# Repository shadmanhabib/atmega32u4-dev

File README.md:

# ATmega32u4-Dev
Development board designed around the ATmega32u4 AVR microcontroller in a small and compact form factor.

## Table of Contents
- [ATmega32u4-Dev](#ATmega32u4-Dev)
  - [Table of Contents](#table-of-contents)
  - [About The Project](#about-the-project)
  - [Getting Started](#getting-started)
    - [Prerequisites](#prerequisites)
    - [Installation](#installation)
  - [Usage](#usage)
  - [Changelog](#changelog)

## About The Project
PCB design, fabrication and documentation of an ATmega32u4 based microcontroller board. 

This project was started to develop a system that could be used for rapid prototyping without the use of external programmers or hardware.
The design was based around the following requirements:

1. On-board programming i.e. not require FTDI or ISP.
2. Remain compatible with Arduno Framework i.e. use Arduino Leonardo pinout.
3. Feature LiPo support.
4. Feature USB-C.

## Getting Started
To get a build this project (or parts thereof), these steps may be followed.

### Prerequisites
1. PlatformIO, Microchip Studios or Arduino IDE for code generation and upload.
2. If you want to make changes to the PCB design or would like to generate new fabrication files, an installation of KiCAD is required.

### Installation
1. Manufacture a PCB.
2. Upload code.

## Usage
Examples will be given in future iterations of this file.

_For more examples, please refer to the [Documentation](https://)_

## Changelog
All notable changes to this project will be documented in this section.

The format is based on [Keep a Changelog](https://keepachangelog.com/en/1.0.0/),
and this project attempts to adhere to [Semantic Versioning](https://semver.org/spec/v2.0.0.html).

### [v1.0.0]
#### Initial design
- ATmega32u4 based design.
- Included LiPo power and charge circuit.
- USB-C for LiPo charging, power and programming.

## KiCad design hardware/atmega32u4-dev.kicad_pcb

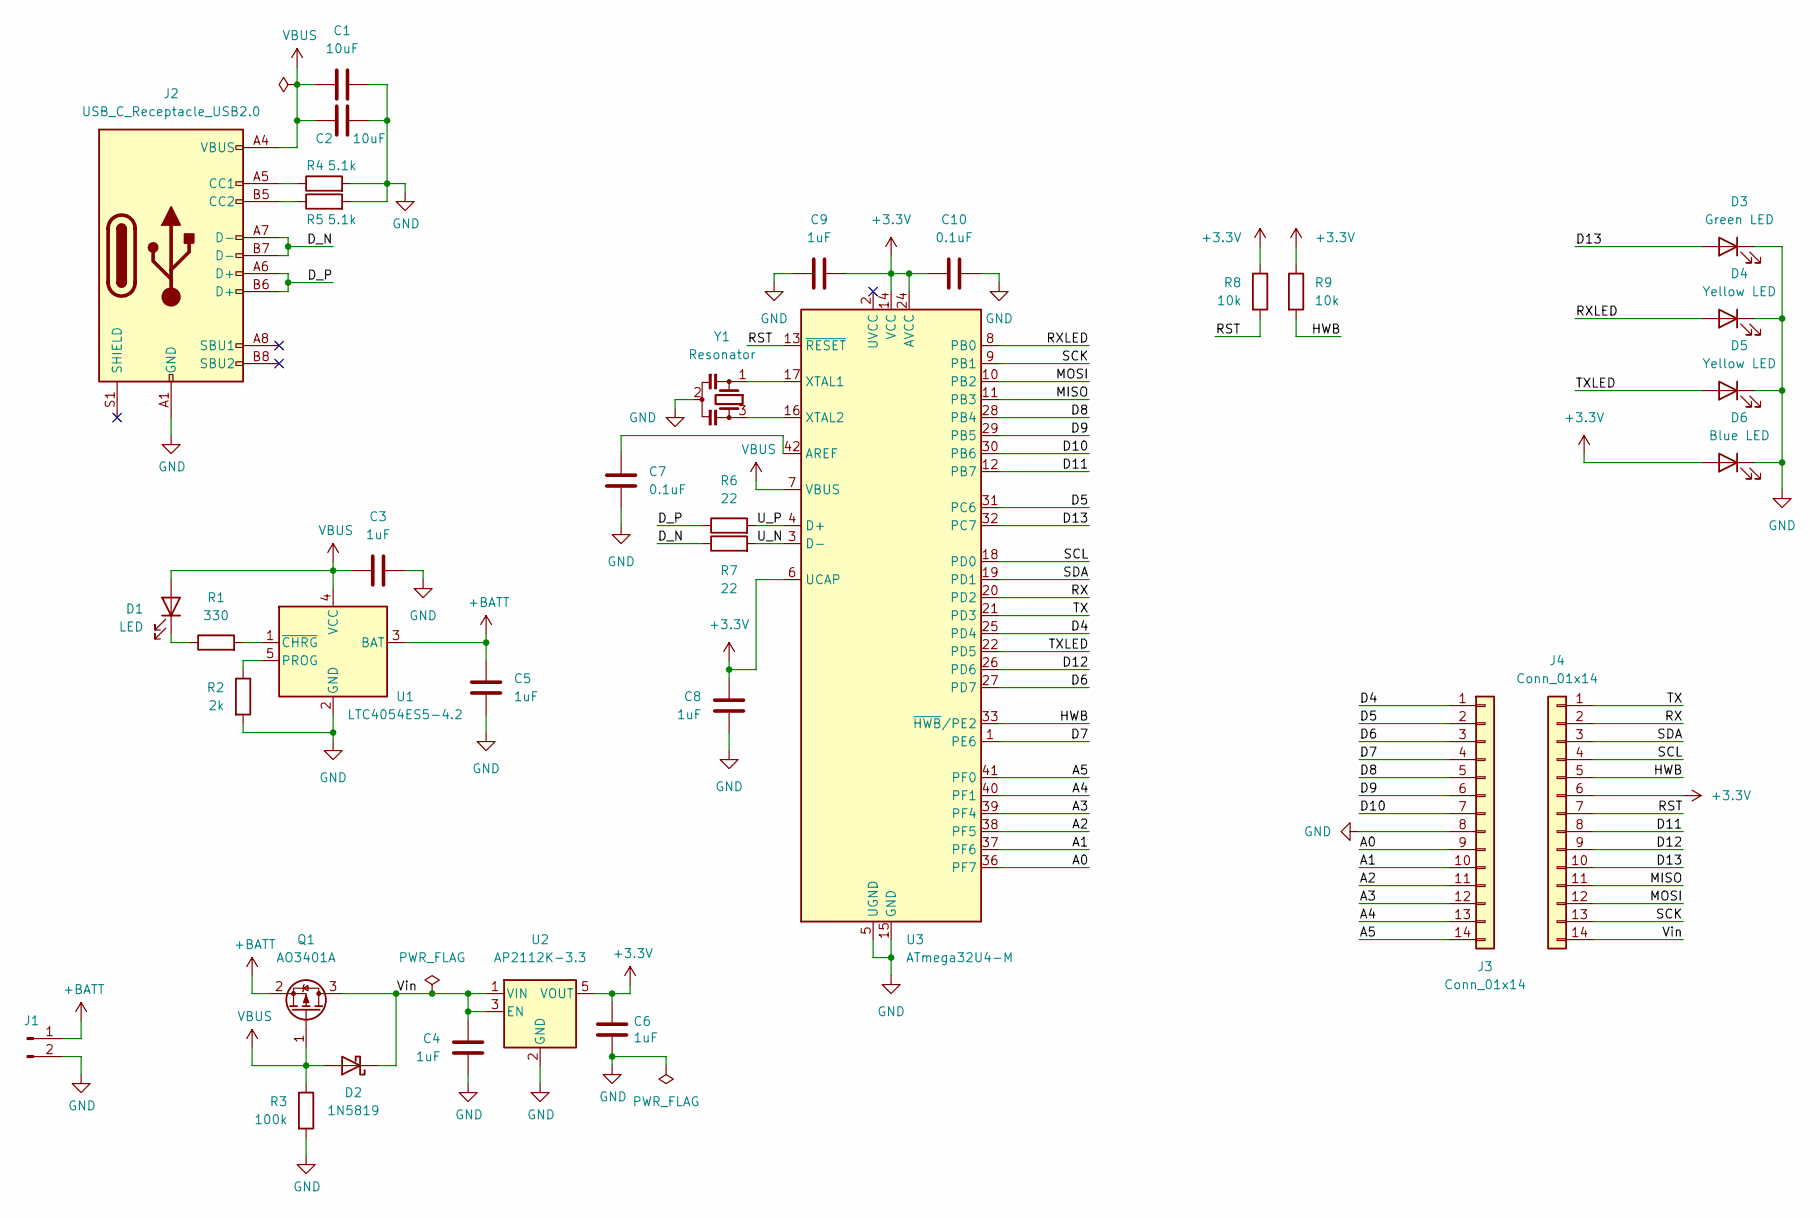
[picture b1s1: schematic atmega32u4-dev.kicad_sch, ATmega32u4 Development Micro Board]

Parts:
C1, C2: 10uF; C_0603_1608Metric
C3, C4, C5, C6, C8, C9: 1uF; C_0603_1608Metric
C7, C10: 0.1uF; C_0603_1608Metric
D1: LED; LED_0603_1608Metric
D2: 1N5819; D_SOD-323
D3: Green LED; LED_0603_1608Metric
D4, D5: Yellow LED; LED_0603_1608Metric
D6: Blue LED; LED_0603_1608Metric
J1: Conn_01x02_Male; JST_PH_S2B-PH-K_1x02_P2.00mm_Horizontal
J2: USB_C_Receptacle_USB2.0; USB_C_Receptacle_Palconn_UTC16-G
J3, J4: Conn_01x14; PinHeader_1x14_P2.54mm_Vertical
Q1: AO3401A; SOT-23
R1: 330; R_0603_1608Metric
R2: 2k; R_0603_1608Metric
R3: 100k; R_0603_1608Metric
R4, R5: 5.1k; R_0603_1608Metric
R6, R7: 22; R_0603_1608Metric
R8, R9: 10k; R_0603_1608Metric
U1: LTC4054ES5-4.2; TSOT-23-5
U2: AP2112K-3.3; SOT-23-5
U3: ATmega32U4-M; QFN-44-1EP_7x7mm_P0.5mm_EP5.2x5.2mm
Y1: Resonator; Resonator_SMD_Murata_CSTxExxV-3Pin_3.0x1.1mm

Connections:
+3V3: C6.1, C8.1, C9.1, C10.1, D6.2 (A), J4.6, R8.1, R9.1, U2.5 (VOUT), U3.6 (UCAP), U3.14 (VCC), U3.24 (AVCC), U3.34 (VCC), U3.44 (AVCC)
+BATT: C5.2, J1.1, Q1.2 (S), U1.3 (BAT)
/A0: J3.9, U3.36 (PF7)
/A1: J3.10, U3.37 (PF6)
/A2: J3.11, U3.38 (PF5)
/A3: J3.12, U3.39 (PF4)
/A4: J3.13, U3.40 (PF1)
/A5: J3.14, U3.41 (PF0)
/D4: J3.1, U3.25 (PD4)
/D5: J3.2, U3.31 (PC6)
/D6: J3.3, U3.27 (PD7)
/D7: J3.4, U3.1 (PE6)
/D8: J3.5, U3.28 (PB4)
/D9: J3.6, U3.29 (PB5)
/D10: J3.7, U3.30 (PB6)
/D11: J4.8, U3.12 (PB7)
/D12: J4.9, U3.26 (PD6)
/D13: D3.2 (A), J4.10, U3.32 (PC7)
/D_N: J2.A7 (D-), J2.B7 (D-), R7.1
/D_P: J2.A6 (D+), J2.B6 (D+), R6.1
/HWB: J4.5, R9.2, U3.33 (~HWB/PE2)
/MISO: J4.11, U3.11 (PB3)
/MOSI: J4.12, U3.10 (PB2)
/RST: J4.7, R8.2, U3.13 (~RESET)
/RX: J4.2, U3.20 (PD2)
/RXLED: D4.2 (A), U3.8 (PB0)
/SCK: J4.13, U3.9 (PB1)
/SCL: J4.4, U3.18 (PD0)
/SDA: J4.3, U3.19 (PD1)
/TX: J4.1, U3.21 (PD3)
/TXLED: D5.2 (A), U3.22 (PD5)
/U_N: R7.2, U3.3 (D-)
/U_P: R6.2, U3.4 (D+)
/Vin: C4.1, D2.1 (K), J4.14, Q1.3 (D), U2.1 (VIN), U2.3 (EN)
GND: C1.2, C2.2, C3.2, C4.2, C5.1, C6.2, C7.2, C8.2, C9.2, C10.2, D3.1 (K), D4.1 (K), D5.1 (K), D6.1 (K), J1.2, J2.A1 (GND), J2.A12 (GND), J2.B1 (GND), J2.B12 (GND), J3.8, R2.2, R3.2, R4.2, R5.2, U1.2 (GND), U2.2 (GND), U3.5 (UGND), U3.15 (GND), U3.23 (GND), U3.35 (GND), U3.43 (GND), U3.45 (GND), Y1.2
unnamed: C7.1, U3.42 (AREF)
unnamed: D1.1 (K), R1.1
unnamed: J2.A5 (CC1), R4.1
unnamed: J2.B5 (CC2), R5.1
unnamed: R1.2, U1.1 (~CHRG)
unnamed: R2.1, U1.5 (PROG)
unnamed: U3.16 (XTAL2), Y1.3
unnamed: U3.17 (XTAL1), Y1.1
VBUS: C1.1, C2.1, C3.1, D1.2 (A), D2.2 (A), J2.A4 (VBUS), J2.A9 (VBUS), J2.B4 (VBUS), J2.B9 (VBUS), Q1.1 (G), R3.1, U1.4 (VCC), U3.7 (VBUS)

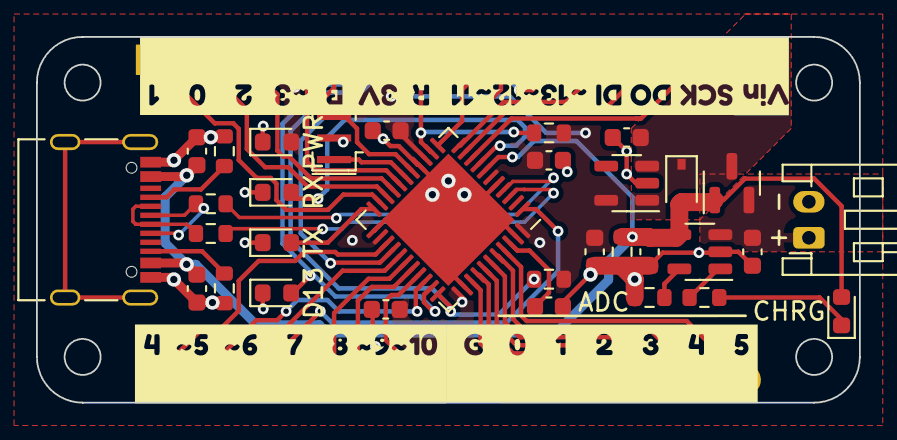
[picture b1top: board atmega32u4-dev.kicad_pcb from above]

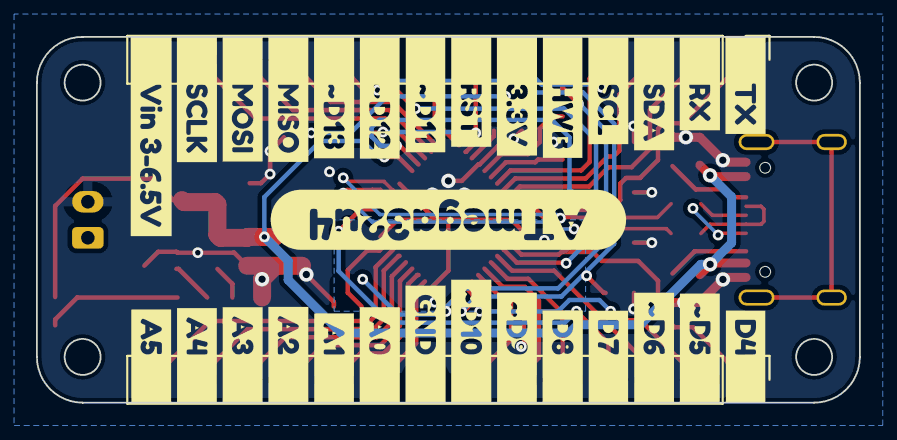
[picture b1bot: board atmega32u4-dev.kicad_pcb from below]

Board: 2 copper layers, 45.7 x 20.3 mm, 70 parts (31 on the bottom side), 44 nets.

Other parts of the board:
kibuzzard-63FC0A8C: G***; kibuzzard-63FC0A8C
kibuzzard-63FC0C67: G***; kibuzzard-63FC0C67
kibuzzard-63FC0D8E: G***; kibuzzard-63FC0D8E
kibuzzard-63FC0E25: G***; kibuzzard-63FC0E25
kibuzzard-63FC1D99: G***; kibuzzard-63FC1D99
kibuzzard-63FC1DA9: G***; kibuzzard-63FC1DA9
kibuzzard-63FC1DB5: G***; kibuzzard-63FC1DB5
kibuzzard-63FC1DBD: G***; kibuzzard-63FC1DBD
kibuzzard-63FC1DF3: G***; kibuzzard-63FC1DF3
kibuzzard-63FC1EB5: G***; kibuzzard-63FC1EB5
kibuzzard-63FC1EBD: G***; kibuzzard-63FC1EBD
kibuzzard-63FC1EC6: G***; kibuzzard-63FC1EC6
kibuzzard-63FC1F6E: G***; kibuzzard-63FC1F6E
kibuzzard-63FC1F7A: G***; kibuzzard-63FC1F7A
kibuzzard-63FC1F52: G***; kibuzzard-63FC1F52
kibuzzard-63FC1F60: G***; kibuzzard-63FC1F60
kibuzzard-63FC1F68: G***; kibuzzard-63FC1F68
kibuzzard-63FC1F81: G***; kibuzzard-63FC1F81
kibuzzard-63FC1FBE: G***; kibuzzard-63FC1FBE
kibuzzard-63FC1FCA: G***; kibuzzard-63FC1FCA
kibuzzard-63FC1FD1: G***; kibuzzard-63FC1FD1
kibuzzard-63FC1FE1: G***; kibuzzard-63FC1FE1
kibuzzard-63FC1FE8: G***; kibuzzard-63FC1FE8
kibuzzard-63FC1FF3: G***; kibuzzard-63FC1FF3
kibuzzard-63FC1FFB: G***; kibuzzard-63FC1FFB
kibuzzard-63FC10C2: G***; kibuzzard-63FC10C2
kibuzzard-63FC10EF: G***; kibuzzard-63FC10EF
kibuzzard-63FC11B0: G***; kibuzzard-63FC11B0
kibuzzard-63FC11D2: G***; kibuzzard-63FC11D2
kibuzzard-63FC11DC: G***; kibuzzard-63FC11DC
kibuzzard-63FC11E2: G***; kibuzzard-63FC11E2
kibuzzard-63FC11F1: G***; kibuzzard-63FC11F1
kibuzzard-63FC11F9: G***; kibuzzard-63FC11F9
kibuzzard-63FC107B: G***; kibuzzard-63FC107B
kibuzzard-63FC2005: G***; kibuzzard-63FC2005
kibuzzard-63FC2462: G***; kibuzzard-63FC2462

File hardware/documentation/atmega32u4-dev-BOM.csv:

Comment,Designator,Footprint,LCSC
10uF,"C1,C2",Capacitor_SMD:C_0603_1608Metric,C96446
1uF,"C3,C4,C5,C6,C8,C9",Capacitor_SMD:C_0603_1608Metric,C15849
0.1uF,"C7,C10",Capacitor_SMD:C_0603_1608Metric,C14663
LED,D1,LED_SMD:LED_0603_1608Metric,C2286
1N5819,D2,Diode_SMD:D_SOD-323,C191023
Green LED,D3,LED_SMD:LED_0603_1608Metric,C72043
Yellow LED,"D4,D5",LED_SMD:LED_0603_1608Metric,C72038
Blue LED,D6,LED_SMD:LED_0603_1608Metric,C72041
USB_C_Receptacle_USB2.0,J2,Connector_USB:USB_C_Receptacle_Palconn_UTC16-G,C2927038
AO3401A,Q1,Package_TO_SOT_SMD:SOT-23,C15127
330,R1,Resistor_SMD:R_0603_1608Metric,C23138
2k,R2,Resistor_SMD:R_0603_1608Metric,C22975
100k,R3,Resistor_SMD:R_0603_1608Metric,C25803
5.1k,"R4,R5",Resistor_SMD:R_0603_1608Metric,C23186
22,"R6,R7",Resistor_SMD:R_0603_1608Metric,C22950
10k,"R8,R9",Resistor_SMD:R_0603_1608Metric,C25804
LTC4054ES5-4.2,U1,Package_TO_SOT_SMD:TSOT-23-5,C32574
AP2112K-3.3,U2,Package_TO_SOT_SMD:SOT-23-5,C51118
ATmega32U4-M,U3,Package_DFN_QFN:QFN-44-1EP_7x7mm_P0.5mm_EP5.2x5.2mm,C112161
Resonator,Y1,Crystal:Resonator_SMD_Murata_CSTxExxV-3Pin_3.0x1.1mm,C341523

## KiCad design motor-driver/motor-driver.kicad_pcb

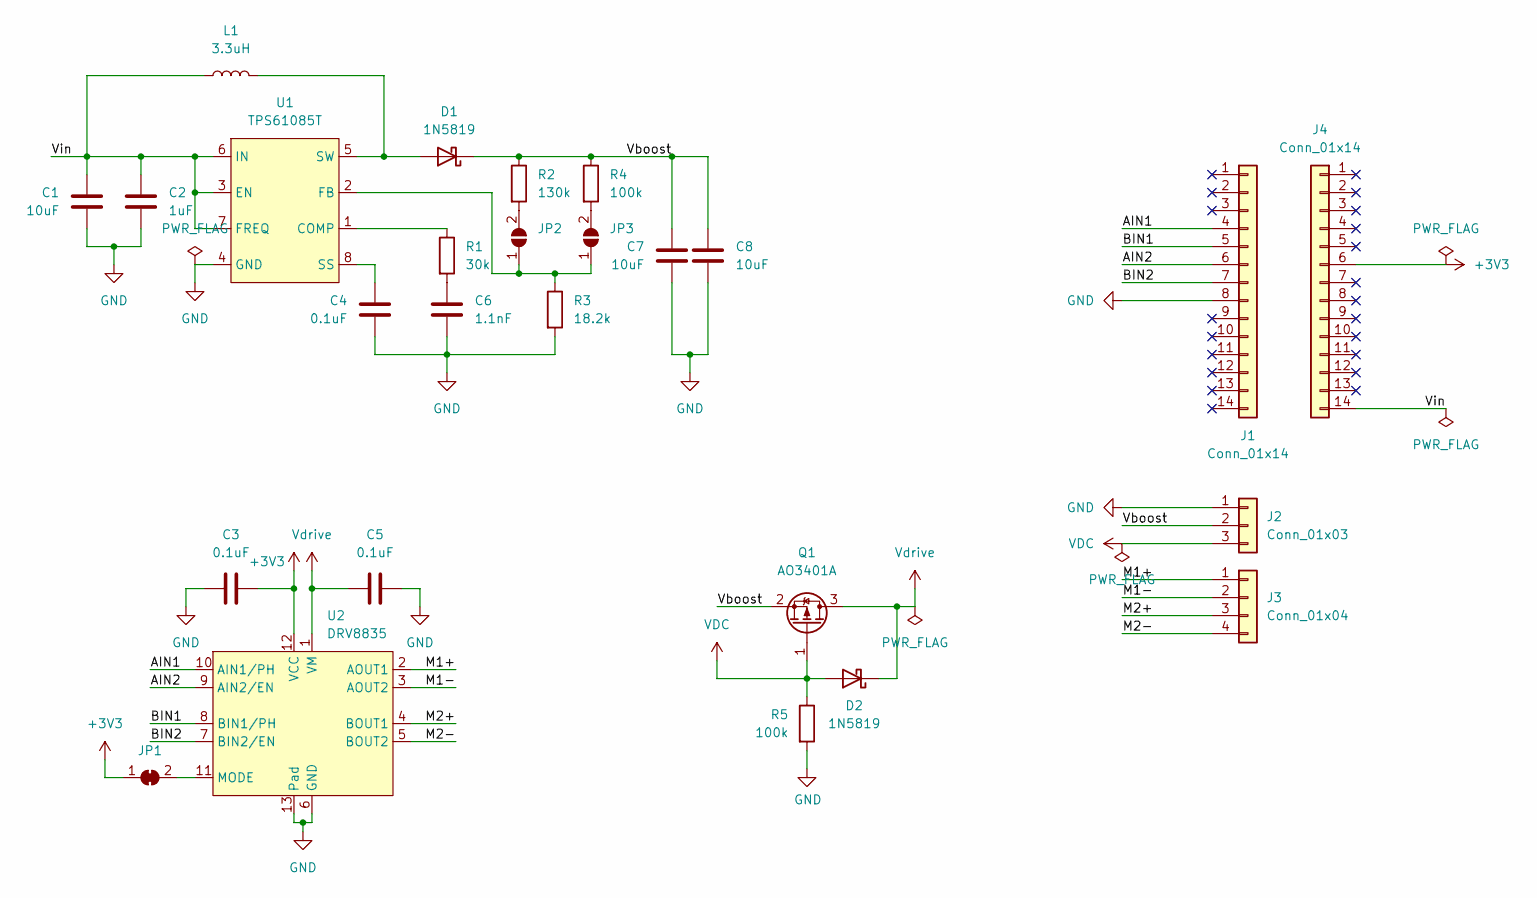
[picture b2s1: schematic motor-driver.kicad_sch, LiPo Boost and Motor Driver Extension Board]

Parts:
C1, C7, C8: 10uF; C_1206_3216Metric
C2: 1uF; C_0603_1608Metric
C3, C4, C5: 0.1uF; C_0603_1608Metric
C6: 1.1nF; C_0603_1608Metric
D1, D2: 1N5819; D_SOD-123
J1, J4: Conn_01x14; PinHeader_1x14_P2.54mm_Vertical
J2: Conn_01x03; PinHeader_1x03_P2.54mm_Vertical
J3: Conn_01x04; PinHeader_1x04_P2.54mm_Vertical
JP1: SolderJumper_2_Bridged; SolderJumper-2_P1.3mm_Bridged_RoundedPad1.0x1.5mm
JP2, JP3: SolderJumper_2_Open; SolderJumper-2_P1.3mm_Open_RoundedPad1.0x1.5mm
L1: 3.3uH; L_6.3x6.3_H3
Q1: AO3401A; SOT-23
R1: 30k; R_0603_1608Metric
R2: 130k; R_0603_1608Metric
R3: 18.2k; R_0603_1608Metric
R4, R5: 100k; R_0603_1608Metric
U1: TPS61085T; VSSOP-8_3.0x3.0mm_P0.65mm
U2: DRV8835; WSON-12-1EP_3x2mm_P0.5mm_EP1x2.65

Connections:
+3V3: C3.2, J4.6, JP1.1 (A), U2.12 (VCC)
/AIN1: J1.4, U2.10 (AIN1/PH)
/AIN2: J1.6, U2.9 (AIN2/EN)
/BIN1: J1.5, U2.8 (BIN1/PH)
/BIN2: J1.7, U2.7 (BIN2/EN)
/M1+: J3.1, U2.2 (AOUT1)
/M1-: J3.2, U2.3 (AOUT2)
/M2+: J3.3, U2.4 (BOUT1)
/M2-: J3.4, U2.5 (BOUT2)
/Vboost: C7.1, C8.1, D1.1 (K), J2.2, Q1.2 (S), R2.1, R4.1
/Vin: C1.1, C2.1, J4.14, L1.1, U1.3 (EN), U1.6 (IN), U1.7 (FREQ)
GND: C1.2, C2.2, C3.1, C4.2, C5.2, C6.2, C7.2, C8.2, J1.8, J2.1, R3.2, R5.2, U1.4 (GND), U2.6 (GND), U2.13 (Pad)
unnamed: C4.1, U1.8 (SS)
unnamed: C6.1, R1.2
unnamed: D1.2 (A), L1.2, U1.5 (SW)
unnamed: JP1.2 (B), U2.11 (MODE)
unnamed: JP2.1 (A), JP3.1 (A), R3.1, U1.2 (FB)
unnamed: JP2.2 (B), R2.2
unnamed: JP3.2 (B), R4.2
unnamed: R1.1, U1.1 (COMP)
VDC: D2.2 (A), J2.3, Q1.1 (G), R5.1
Vdrive: C5.1, D2.1 (K), Q1.3 (D), U2.1 (VM)

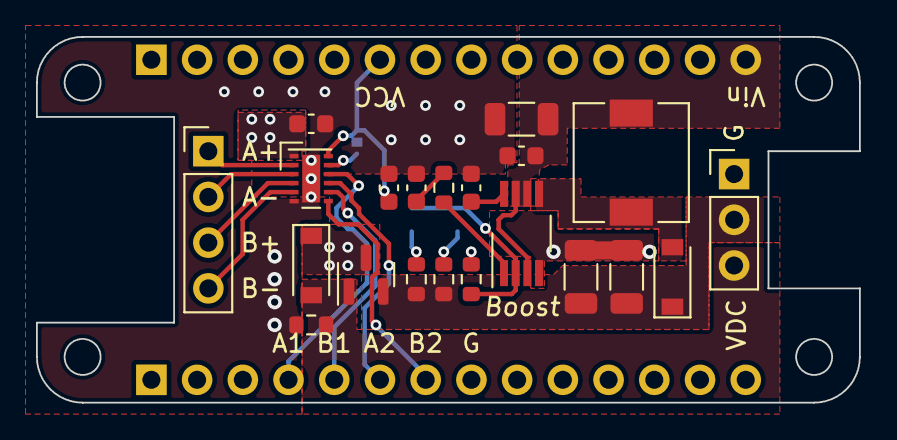
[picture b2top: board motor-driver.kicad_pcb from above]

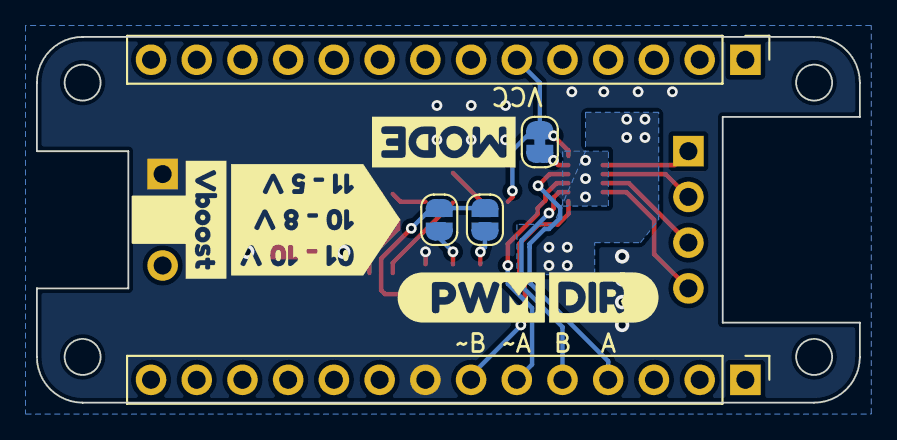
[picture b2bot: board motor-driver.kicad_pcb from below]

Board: 2 copper layers, 45.7 x 20.3 mm, 31 parts (10 on the bottom side), 22 nets.

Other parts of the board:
kibuzzard-6471BDC6: G***; kibuzzard-6471BDC6
kibuzzard-6471BDE7: G***; kibuzzard-6471BDE7
kibuzzard-6471BF11: G***; kibuzzard-6471BF11
kibuzzard-6471C20C: G***; kibuzzard-6471C20C
kibuzzard-6471C159: G***; kibuzzard-6471C159

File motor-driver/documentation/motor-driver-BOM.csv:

Comment,Designator,Footprint,LCSC
"10uF","C1,C7,C8","Capacitor_SMD:C_1206_3216Metric",""
"1uF","C2","Capacitor_SMD:C_0603_1608Metric",""
"0.1uF","C3,C4,C5","Capacitor_SMD:C_0603_1608Metric",""
"1.1nF","C6","Capacitor_SMD:C_0603_1608Metric",""
"1N5819","D1,D2","Diode_SMD:D_SOD-123",""
"SolderJumper_2_Bridged","JP1","Jumper:SolderJumper-2_P1.3mm_Bridged_RoundedPad1.0x1.5mm",""
"SolderJumper_2_Open","JP2,JP3","Jumper:SolderJumper-2_P1.3mm_Open_RoundedPad1.0x1.5mm",""
"3.3uH","L1","Inductor_SMD:L_6.3x6.3_H3",""
"AO3401A","Q1","Package_TO_SOT_SMD:SOT-23",""
"30k","R1","Resistor_SMD:R_0603_1608Metric",""
"130k","R2","Resistor_SMD:R_0603_1608Metric",""
"18.2k","R3","Resistor_SMD:R_0603_1608Metric",""
"100k","R4,R5","Resistor_SMD:R_0603_1608Metric",""
"TPS61085T","U1","Package_SO:VSSOP-8_3.0x3.0mm_P0.65mm",""
"DRV8835","U2","Package_SON:WSON-12-1EP_3x2mm_P0.5mm_EP1x2.65",""

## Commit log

2023-02-22 Initial commit
    Setup folder structure, KiCAD files and README.
2023-02-24 Schematic first draft
    First iteration of dev board schematic.
2023-02-27 Completed PCB layout
    Completed PCB layout for manufacture.
2023-05-27 Completed v1.0.0
    Added files for LiPo boost and motor driver board. Completed schematic and layout.
2023-05-29 Generated BOM and fabrication files for v1.0.0 boards.
2023-08-26 Code additions for basic testing.
